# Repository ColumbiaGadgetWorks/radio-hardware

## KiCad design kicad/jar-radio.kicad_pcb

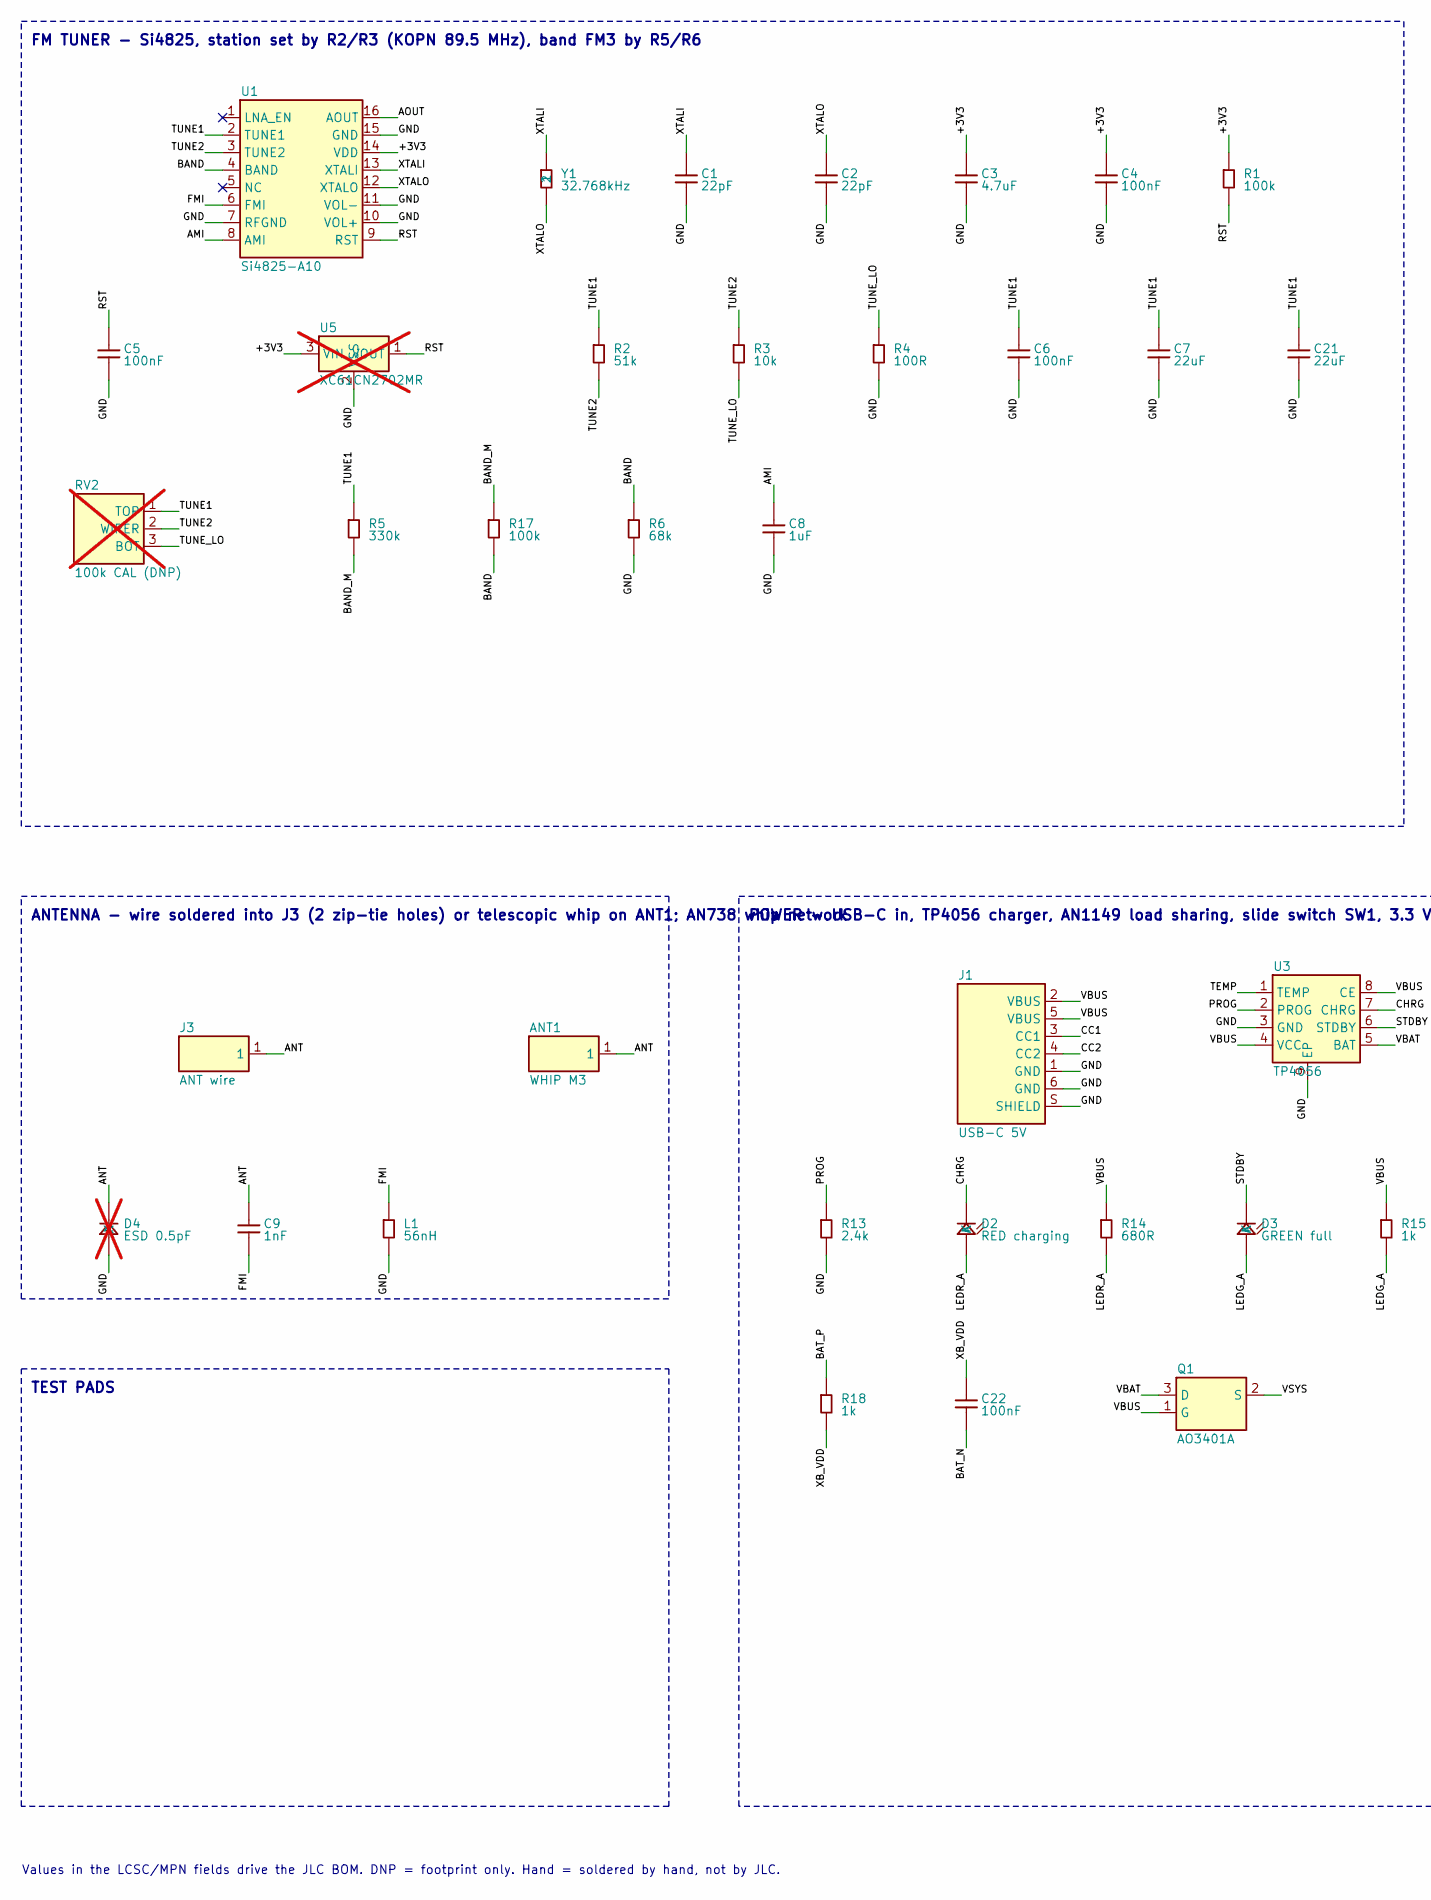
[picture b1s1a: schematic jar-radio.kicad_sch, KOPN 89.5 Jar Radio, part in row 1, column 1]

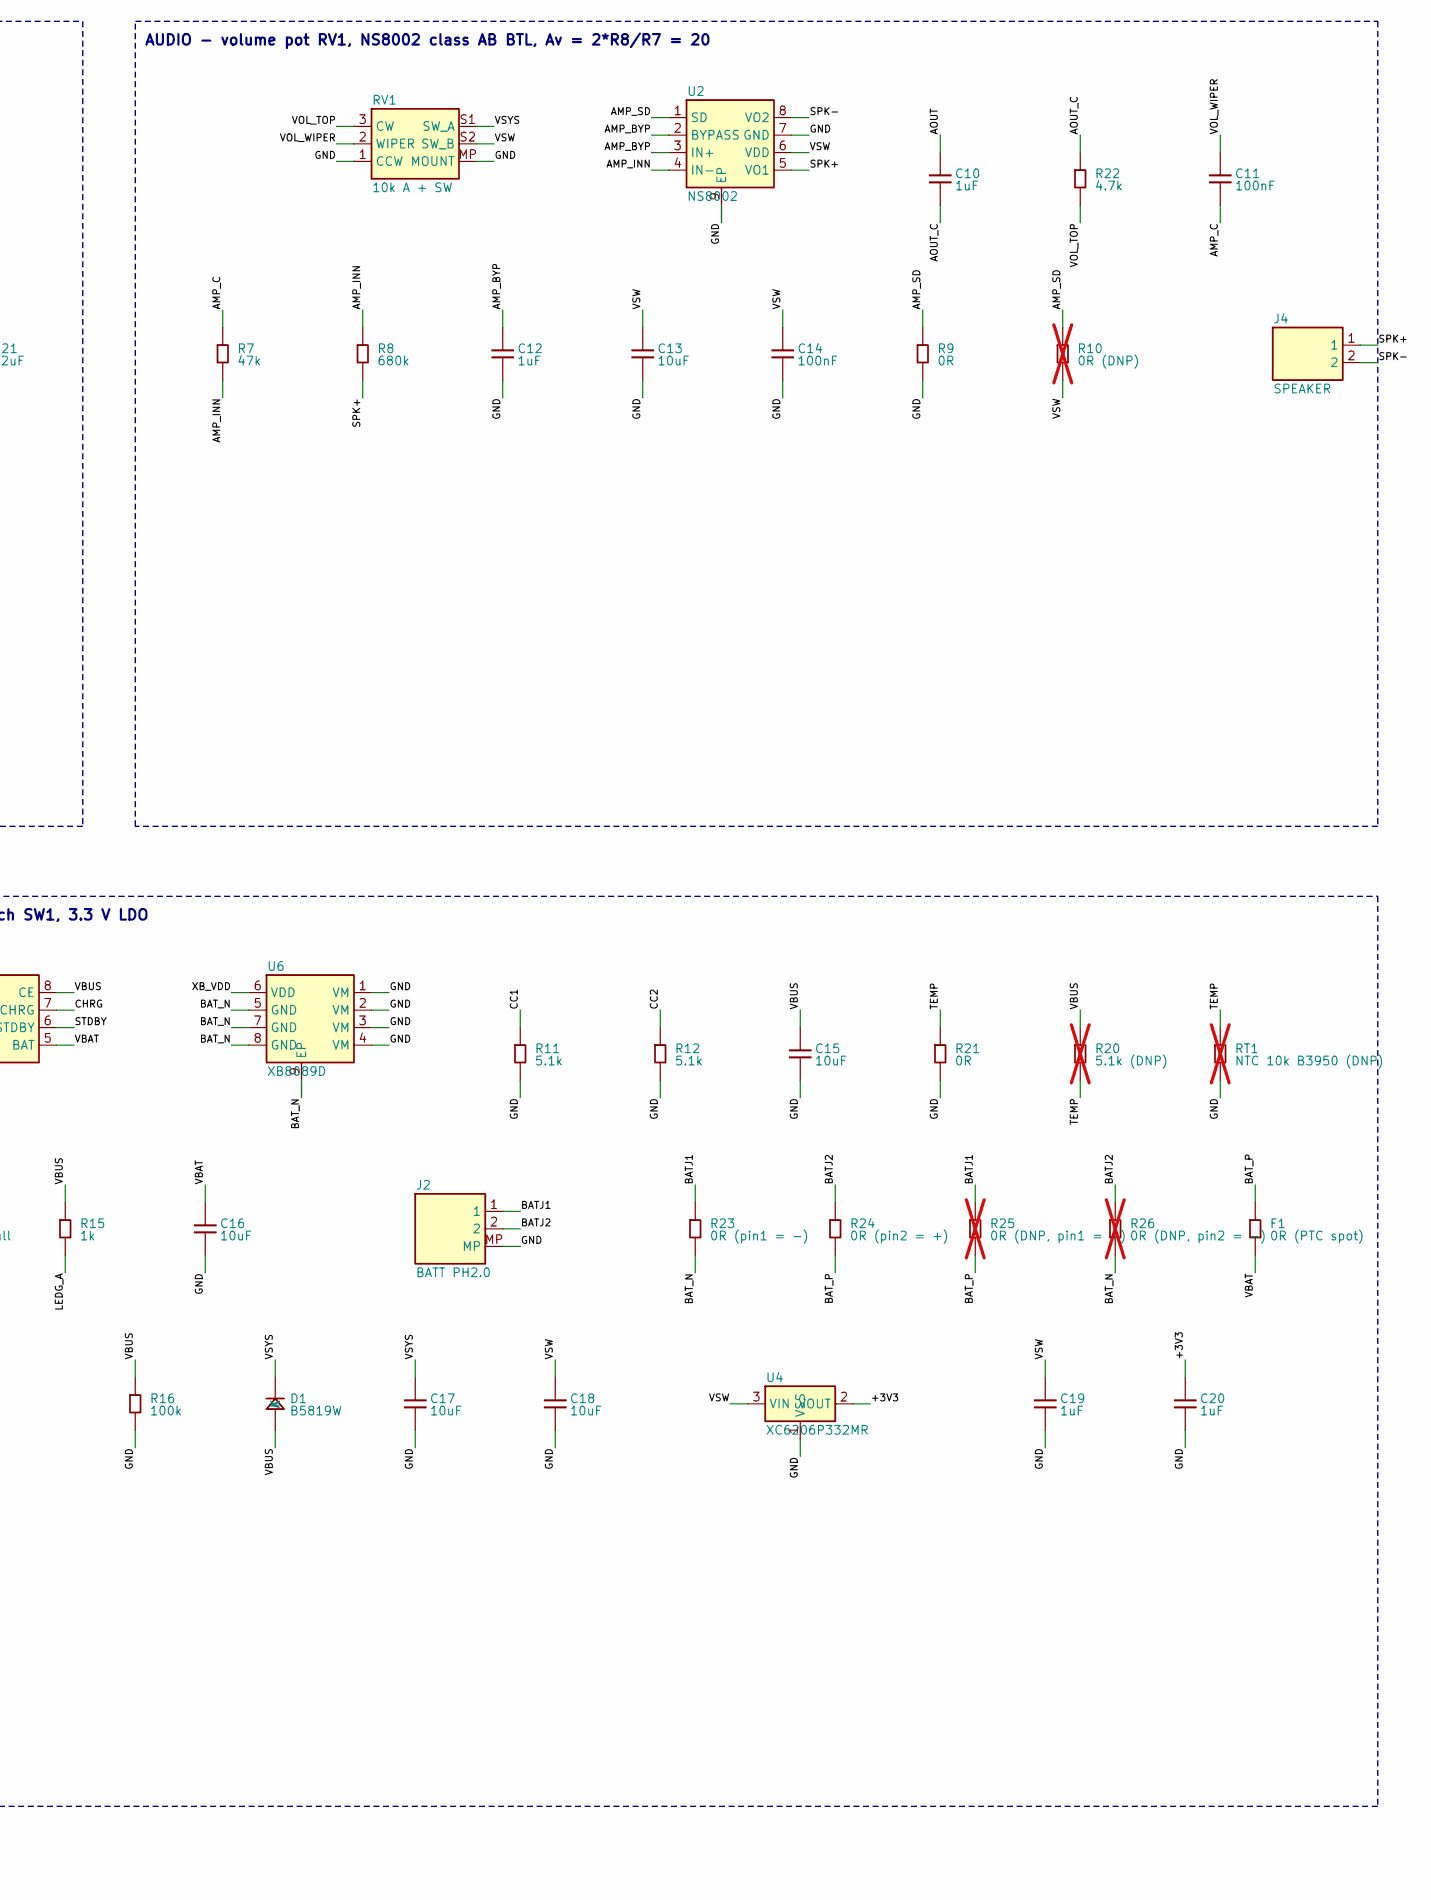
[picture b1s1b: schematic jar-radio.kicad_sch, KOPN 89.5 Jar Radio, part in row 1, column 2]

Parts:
ANT1: WHIP M3; Antenna_Telescopic_M3
C1, C2: 22pF; C_0603_1608Metric; MPN CL10C220JB8NNNC; LCSC C1653
C3: 4.7uF; C_0603_1608Metric; MPN CL10A475KO8NNNC; LCSC C19666
C4, C5, C6, C11, C14, C22: 100nF; C_0603_1608Metric; MPN CC0603KRX7R9BB104; LCSC C14663
C7, C21: 22uF; C_0603_1608Metric; MPN CL10A226MQ8NRNC; LCSC C59461
C8, C10, C12, C19, C20: 1uF; C_0603_1608Metric; MPN CL10A105KB8NNNC; LCSC C15849
C9: 1nF; C_0603_1608Metric; MPN CL10B102KB8NNNC; LCSC C1588
C13, C15, C16, C17, C18: 10uF; C_0603_1608Metric; MPN CL10A106KP8NNNC; LCSC C19702
D1: B5819W; D_SOD-123; MPN B5819W SL; LCSC C8598
D2: RED charging; LED_0603_1608Metric; MPN KT-0603R; LCSC C2286
D3: GREEN full; LED_0805_2012Metric; MPN KT-0805G; LCSC C2297
D4: ESD 0.5pF; D_SOD-882; MPN SP3021-01ETG; LCSC C126839; not fitted
F1: 0R (PTC spot); Fuse_1206_3216Metric; MPN 1206W4F0000T5E; LCSC C17888
J1: USB-C 5V; USB_C_Receptacle_ShouHan_TYPE-C-6P-LTH6.8-108_Vertical; MPN TYPE-C 6P LTH6.8 108; LCSC C30167335
J2: BATT PH2.0; Battery_PH2.0_RightAngle_SMD_PlugCutout; MPN ZX-PH2.0-WT2P; LCSC C7429689
J3: ANT wire; Antenna_Wire_Solder_D2.0
J4: SPEAKER; Speaker_HDK-4008BB-2_TopMount; MPN HDK-4008BB-2 (C22371323, hand-soldered 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
L1: 56nH; L_0603_1608Metric; MPN LQW18AN56NJ00D; LCSC C98080
Q1: AO3401A; SOT-23; MPN AO3401A; LCSC C15127
R1, R16, R17: 100k; R_0603_1608Metric; MPN 0603WAF1003T5E; LCSC C25803
R2: 51k; R_0603_1608Metric; MPN 0603WAF5102T5E; LCSC C23196
R3: 10k; R_0603_1608Metric; MPN 0603WAF1002T5E; LCSC C25804
R4: 100R; R_0603_1608Metric; MPN 0603WAF1000T5E; LCSC C22775
R5: 330k; R_0603_1608Metric; MPN 0603WAF3303T5E; LCSC C23137
R6: 68k; R_0603_1608Metric; MPN 0603WAF6802T5E; LCSC C23231
R7: 47k; R_0603_1608Metric; MPN 0603WAF4702T5E; LCSC C25819
R8: 680k; R_0603_1608Metric; MPN 0603WAF6803T5E; LCSC C25822
R9, R21: 0R; R_0603_1608Metric; MPN 0603WAF0000T5E; LCSC C21189
R10: 0R (DNP); R_0603_1608Metric; MPN 0603WAF0000T5E; LCSC C21189; not fitted
R11, R12: 5.1k; R_0603_1608Metric; MPN 0603WAF5101T5E; LCSC C23186
R13: 2.4k; R_0603_1608Metric; MPN 0603WAF2401T5E; LCSC C22940
R14: 680R; R_0603_1608Metric; MPN 0603WAF6800T5E; LCSC C23228
R15, R18: 1k; R_0603_1608Metric; MPN 0603WAF1001T5E; LCSC C21190
R20: 5.1k (DNP); R_0603_1608Metric; MPN 0603WAF5101T5E; LCSC C23186; not fitted
R22: 4.7k; R_0603_1608Metric; MPN 0603WAF4701T5E; LCSC C23162
R23: 0R (pin1 = -); R_1206_3216Metric; MPN 1206W4F0000T5E; LCSC C17888
R24: 0R (pin2 = +); R_1206_3216Metric; MPN 1206W4F0000T5E; LCSC C17888
R25: 0R (DNP, pin1 = +); R_1206_3216Metric; MPN 1206W4F0000T5E; LCSC C17888; not fitted
R26: 0R (DNP, pin2 = -); R_1206_3216Metric; MPN 1206W4F0000T5E; LCSC C17888; not fitted
RT1: NTC 10k B3950 (DNP); R_0603_1608Metric; MPN SDNT1608X103F3950FTF; LCSC C279936; not fitted
RV1: 10k A + SW; Potentiometer_CTR_R09512NS_RearMount_Switch; MPN R09512NS-FB15S7.0-A103-00G; LCSC C18213422
RV2: 100k CAL (DNP); PinHeader_1x03_P2.54mm_Vertical; MPN 3296W-1-104; not fitted
U1: Si4825-A10; SOIC-16_3.9x9.9mm_P1.27mm; MPN SI4825-A10-CSR; LCSC C2654605
U2: NS8002; SOIC-8-1EP_3.9x4.9mm_P1.27mm_EP2.41x3.3mm; MPN NS8002; LCSC C189960
U3: TP4056; SOIC-8-1EP_3.9x4.9mm_P1.27mm_EP2.29x3mm; MPN TP4056-42-ESOP8; LCSC C16581
U4: XC6206P332MR; SOT-23; MPN XC6206P332MR; LCSC C5446
U5: XC61CN2702MR; SOT-23; MPN XC61CN2702MR-G; LCSC C112139; not fitted
U6: XB8089D; SOIC-8-1EP_3.9x4.9mm_P1.27mm_EP2.41x3.3mm; MPN XB8089D; LCSC C79928
Y1: 32.768kHz; Crystal_SMD_3215-2Pin_3.2x1.5mm; MPN Q13FC13500004; LCSC C32346

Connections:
+3V3: C3.1, C4.1, C20.1, R1.1, U1.14 (VDD), U4.2 (VOUT), U5.3 (VIN)
AMI: C8.1, U1.8 (AMI)
AMP_BYP: C12.1, U2.2 (BYPASS), U2.3 (IN+)
AMP_C: C11.2, R7.1
AMP_INN: R7.2, R8.1, U2.4 (IN-)
AMP_SD: R9.1, R10.1, U2.1 (SD)
ANT: ANT1.1, C9.1, D4.1 (K), J3.1
AOUT: C10.1, U1.16 (AOUT)
AOUT_C: C10.2, R22.1
BAND: R6.1, R17.2, U1.4 (BAND)
BAND_M: R5.2, R17.1
BATJ1: J2.1, R23.1, R25.1
BATJ2: J2.2, R24.1, R26.1
BAT_N: C22.2, R23.2, R26.2, U6.5 (GND), U6.7 (GND), U6.8 (GND), U6.9 (EP)
BAT_P: F1.1, R18.1, R24.2, R25.2
CC1: J1.3 (CC1), R11.1
CC2: J1.4 (CC2), R12.1
CHRG: D2.1 (K), U3.7 (CHRG)
FMI: C9.2, L1.1, U1.6 (FMI)
GND: C1.2, C2.2, C3.2, C4.2, C5.2, C6.2, C7.2, C8.2, C12.2, C13.2, C14.2, C15.2, C16.2, C17.2, C18.2, C19.2, C20.2, C21.2, D4.2 (A), J1.1 (GND), J1.6 (GND), J1.S (SHIELD), J2.MP, L1.2, R4.2, R6.2, R9.2, R11.2, R12.2, R13.2, R16.2, R21.2, RT1.2, RV1.1 (CCW), RV1.MP (MOUNT), U1.7 (RFGND), U1.10 (VOL+), U1.11 (VOL-), U1.15 (GND), U2.7 (GND), U2.9 (EP), U3.3 (GND), U3.9 (EP), U4.1 (VSS), U5.2 (VSS), U6.1 (VM), U6.2 (VM), U6.3 (VM), U6.4 (VM)
LEDG_A: D3.2 (A), R15.2
LEDR_A: D2.2 (A), R14.2
PROG: R13.1, U3.2 (PROG)
RST: C5.1, R1.2, U1.9 (RST), U5.1 (VOUT)
SPK+: J4.1, R8.2, U2.5 (VO1)
SPK-: J4.2, U2.8 (VO2)
STDBY: D3.1 (K), U3.6 (STDBY)
TEMP: R20.2, R21.1, RT1.1, U3.1 (TEMP)
TUNE1: C6.1, C7.1, C21.1, R2.1, R5.1, RV2.1 (TOP), U1.2 (TUNE1)
TUNE2: R2.2, R3.1, RV2.2 (WIPER), U1.3 (TUNE2)
TUNE_LO: R3.2, R4.1, RV2.3 (BOT)
VBAT: C16.1, F1.2, Q1.3 (D), U3.5 (BAT)
VBUS: C15.1, D1.2 (A), J1.2 (VBUS), J1.5 (VBUS), Q1.1 (G), R14.1, R15.1, R16.1, R20.1, U3.4 (VCC), U3.8 (CE)
VOL_TOP: R22.2, RV1.3 (CW)
VOL_WIPER: C11.1, RV1.2 (WIPER)
VSW: C13.1, C14.1, C18.1, C19.1, R10.2, RV1.S2 (SW_B), U2.6 (VDD), U4.3 (VIN)
VSYS: C17.1, D1.1 (K), Q1.2 (S), RV1.S1 (SW_A)
XB_VDD: C22.1, R18.2, U6.6 (VDD)
XTALI: C1.1, U1.13 (XTALI), Y1.1
XTALO: C2.1, U1.12 (XTALO), Y1.2

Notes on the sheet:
FM TUNER - Si4825, station set by R2/R3 (KOPN 89.5 MHz), band FM3 by R5/R6
ANTENNA - wire soldered into J3 (2 zip-tie holes) or telescopic whip on ANT1; AN738 whip network
AUDIO - volume pot RV1, NS8002 class AB BTL, Av = 2*R8/R7 = 20
POWER - USB-C in, TP4056 charger, AN1149 load sharing, slide switch SW1, 3.3 V LDO
TEST PADS
Values in the LCSC/MPN fields drive the JLC BOM. DNP = footprint only. Hand = soldered by hand, not by JLC.

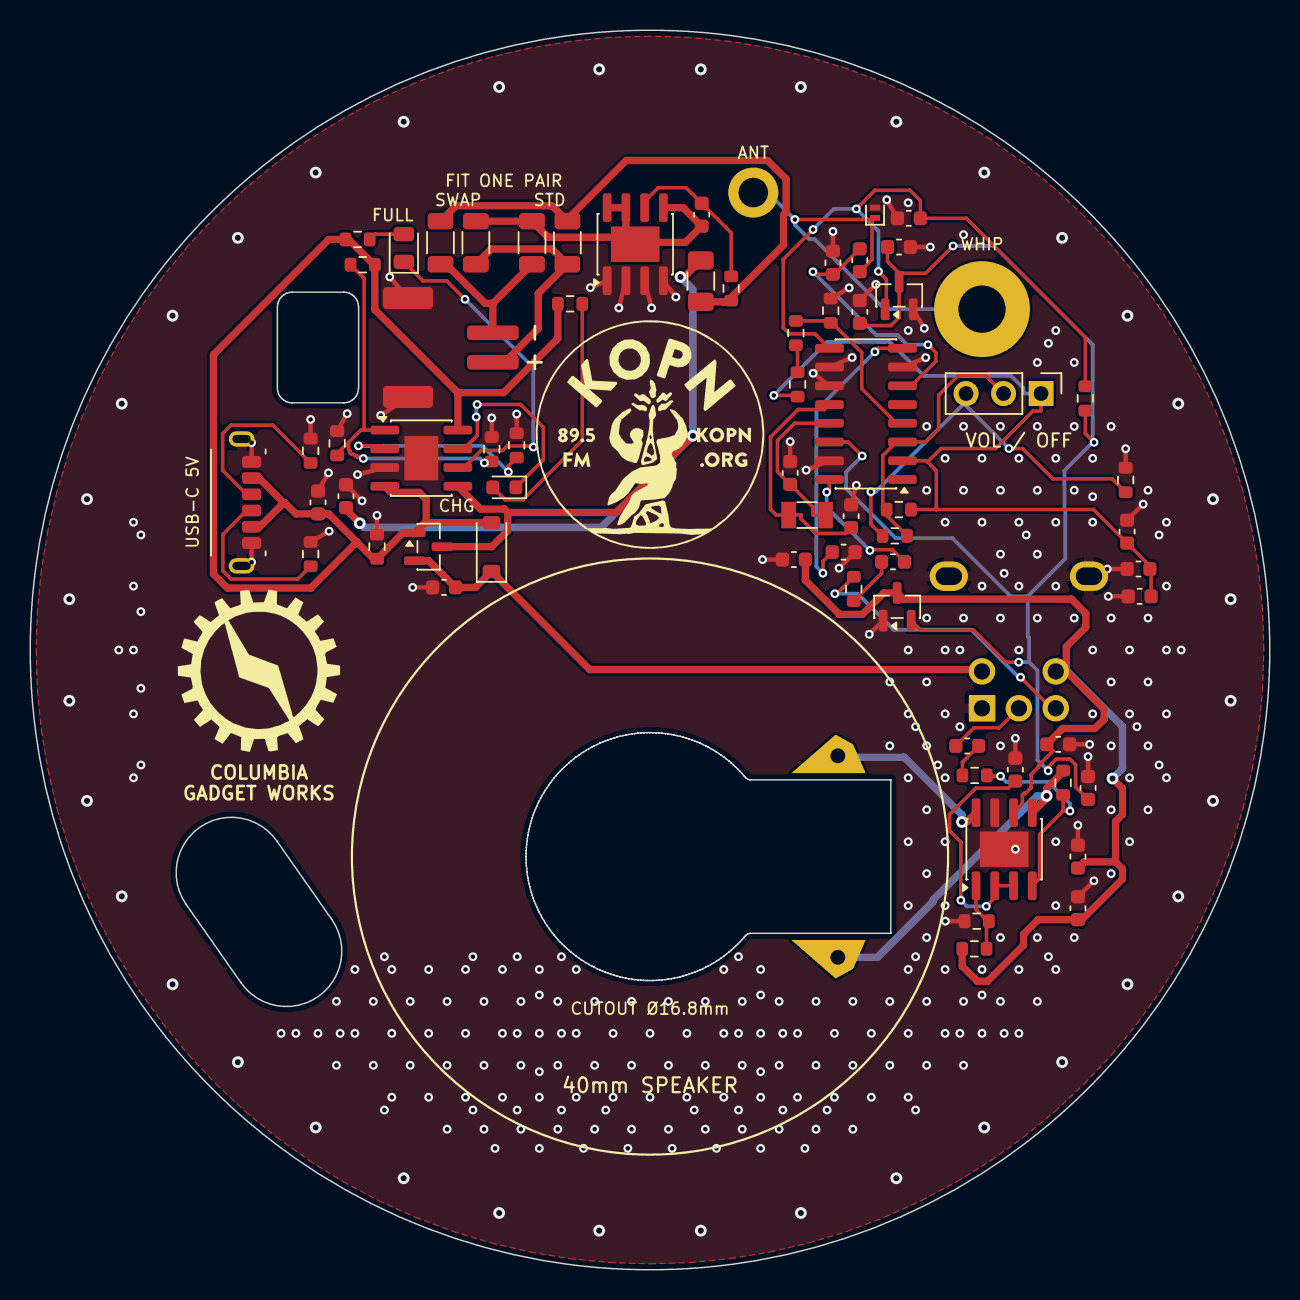
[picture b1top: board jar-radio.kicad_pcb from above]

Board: 2 copper layers, 84.0 x 84.0 mm, 72 parts (1 on the bottom side), 40 nets.

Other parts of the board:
MK1: Battery_LiPo_102050_Outline
MK2: Logo_KOPN_Circle_15.5mm
MK3: Logo_CGW_11mm

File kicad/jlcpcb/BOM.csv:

Comment,Designator,Footprint,LCSC Part #,MPN,Qty
22pF,"C1,C2",C_0603_1608Metric,C1653,CL10C220JB8NNNC,2
10uF,"C13,C15,C16,C17,C18",C_0603_1608Metric,C19702,CL10A106KP8NNNC,5
4.7uF,C3,C_0603_1608Metric,C19666,CL10A475KO8NNNC,1
100nF,"C4,C5,C6,C11,C14,C22",C_0603_1608Metric,C14663,CC0603KRX7R9BB104,6
22uF,"C7,C21",C_0603_1608Metric,C59461,CL10A226MQ8NRNC,2
1uF,"C8,C10,C12,C19,C20",C_0603_1608Metric,C15849,CL10A105KB8NNNC,5
1nF,C9,C_0603_1608Metric,C1588,CL10B102KB8NNNC,1
B5819W,D1,D_SOD-123,C8598,B5819W SL,1
RED charging,D2,LED_0603_1608Metric,C2286,KT-0603R,1
GREEN full,D3,LED_0805_2012Metric,C2297,KT-0805G,1
0R (PTC spot),F1,Fuse_1206_3216Metric,C17888,1206W4F0000T5E,1
USB-C 5V,J1,USB_C_Receptacle_ShouHan_TYPE-C-6P-LTH6.8-108_Vertical,C30167335,TYPE-C 6P LTH6.8 108,1
BATT PH2.0,J2,Battery_PH2.0_RightAngle_SMD_PlugCutout,C7429689,ZX-PH2.0-WT2P,1
56nH,L1,L_0603_1608Metric,C98080,LQW18AN56NJ00D,1
AO3401A,Q1,SOT-23,C15127,AO3401A,1
100k,"R1,R16,R17",R_0603_1608Metric,C25803,0603WAF1003T5E,3
5.1k,"R11,R12",R_0603_1608Metric,C23186,0603WAF5101T5E,2
2.4k,R13,R_0603_1608Metric,C22940,0603WAF2401T5E,1
680R,R14,R_0603_1608Metric,C23228,0603WAF6800T5E,1
1k,"R15,R18",R_0603_1608Metric,C21190,0603WAF1001T5E,2
51k,R2,R_0603_1608Metric,C23196,0603WAF5102T5E,1
4.7k,R22,R_0603_1608Metric,C23162,0603WAF4701T5E,1
0R (pin1 = -),R23,R_1206_3216Metric,C17888,1206W4F0000T5E,1
0R (pin2 = +),R24,R_1206_3216Metric,C17888,1206W4F0000T5E,1
10k,R3,R_0603_1608Metric,C25804,0603WAF1002T5E,1
100R,R4,R_0603_1608Metric,C22775,0603WAF1000T5E,1
330k,R5,R_0603_1608Metric,C23137,0603WAF3303T5E,1
68k,R6,R_0603_1608Metric,C23231,0603WAF6802T5E,1
47k,R7,R_0603_1608Metric,C25819,0603WAF4702T5E,1
680k,R8,R_0603_1608Metric,C25822,0603WAF6803T5E,1
0R,"R9,R21",R_0603_1608Metric,C21189,0603WAF0000T5E,2
10k A + SW,RV1,Potentiometer_CTR_R09512NS_RearMount_Switch,C18213422,R09512NS-FB15S7.0-A103-00G,1
Si4825-A10,U1,SOIC-16_3.9x9.9mm_P1.27mm,C2654605,SI4825-A10-CSR,1
NS8002,U2,SOIC-8-1EP_3.9x4.9mm_P1.27mm_EP2.41x3.3mm,C189960,NS8002,1
TP4056,U3,SOIC-8-1EP_3.9x4.9mm_P1.27mm_EP2.29x3mm,C16581,TP4056-42-ESOP8,1
XC6206P332MR,U4,SOT-23,C5446,XC6206P332MR,1
XB8089D,U6,SOIC-8-1EP_3.9x4.9mm_P1.27mm_EP2.41x3.3mm,C79928,XB8089D,1
32.768kHz,Y1,Crystal_SMD_3215-2Pin_3.2x1.5mm,C32346,Q13FC13500004,1

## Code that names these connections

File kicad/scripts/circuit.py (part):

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     {'2': 'TUNE1', '3': 'TUNE2', '4': 'BAND', '6': 'FMI', '7': 'GND', '8': 'AMI', '9': 'RST',
      '10': 'GND', '11': 'GND', '12': 'XTALO', '13': 'XTALI', '14': '+3V3', '15': 'GND', '16': 'AOUT'},
     block=B, nc=('1', '5'))
part('Y1', 'Crystal', '32.768kHz', 'Crystal:Crystal_SMD_3215-2Pin_3.2x1.5mm', 'C32346', 'Q13FC13500004', {'1': 'XTALI', '2': 'XTALO'}, block=B)
part('C1', 'C', '22pF', C0603, 'C1653', 'CL10C220JB8NNNC', {'1': 'XTALI', '2': 'GND'}, block=B)
part('C2', 'C', '22pF', C0603, 'C1653', 'CL10C220JB8NNNC', {'1': 'XTALO', '2': 'GND'}, block=B)
part('C3', 'C', '4.7uF', C0603, 'C19666', 'CL10A475KO8NNNC', {'1': '+3V3', '2': 'GND'}, block=B)
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     {'1': 'BATJ1', '2': 'BATJ2', 'MP': 'GND'}, block=B, top=True)
# polarity crossover, 1206 0R (same part as F1, easy to move by hand). Fit R23+R24
# (pin 2 = +) OR R25+R26 (pin 1 = +), never both pairs: that shorts the cell.
part('R23', 'R', '0R (pin1 = -)', 'Resistor_SMD:R_1206_3216Metric', 'C17888', '1206W4F0000T5E', {'1': 'BATJ1', '2': 'BAT_N'}, block=B)
part('R24', 'R', '0R (pin2 = +)', 'Resistor_SMD:R_1206_3216Metric', 'C17888', '1206W4F0000T5E', {'1': 'BATJ2', '2': 'BAT_P'}, block=B)
part('R25', 'R', '0R (DNP, pin1 = +)', 'Resistor_SMD:R_1206_3216Metric', 'C17888', '1206W4F0000T5E', {'1': 'BATJ1', '2': 'BAT_P'}, block=B, dnp=True)
part('R26', 'R', '0R (DNP, pin2 = -)', 'Resistor_SMD:R_1206_3216Metric', 'C17888', '1206W4F0000T5E', {'1': 'BATJ2', '2': 'BAT_N'}, block=B, dnp=True)
# protection: PTC in BAT+, XB8089D (OV 4.25 / UV 2.5 V, 10 A OC, 40 A short, reverse cell) in BAT-
# F1 is fitted with a 0R 1206 jumper; upgrade = PTC SMD1206B110TFT (C269119) on the same pads
part('F1', 'R', '0R (PTC spot)', 'Fuse:Fuse_1206_3216Metric', 'C17888', '1206W4F0000T5E', {'1': 'BAT_P', '2': 'VBAT'}, block=B)
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

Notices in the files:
kicad/jar-radio.kicad_pcb:
CERN-OHL-S-2.0
kicad/jar-radio.kicad_sch:
Hardware licence: CERN-OHL-S-2.0
